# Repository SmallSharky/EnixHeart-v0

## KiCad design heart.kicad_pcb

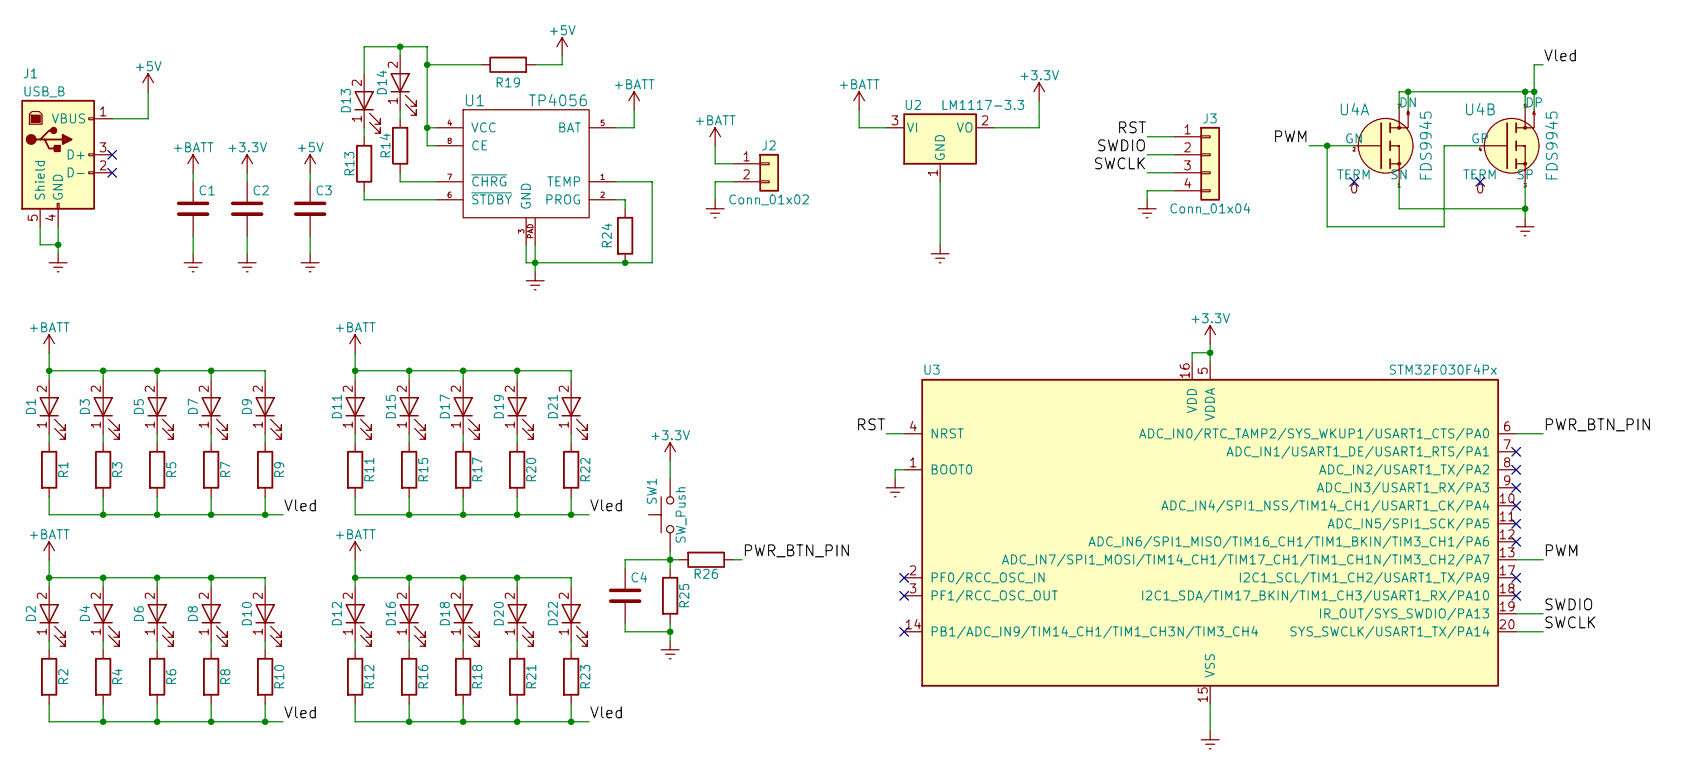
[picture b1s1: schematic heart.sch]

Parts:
C1, C2, C3, C4: C; C_0805_HandSoldering
D1, D2, D3, D4, D5, D6, D7, D8, D9, D10, D11, D12, D13, D14, D15, D16, D17, D18, D19, D20, D21, D22: LED; LED_1206_HandSoldering
J1: USB_B; USB_Micro-B_Molex_47346-0001
J2: Conn_01x02; Pin_Header_Straight_1x02_Pitch2.54mm
J3: Conn_01x04; Pin_Header_Straight_1x04_Pitch2.54mm
R1, R2, R3, R4, R5, R6, R7, R8, R9, R10, R11, R12, R13, R14, R15, R16, R17, R18, R19, R20, R21, R22, R23, R24, R25, R26: R; R_1206_HandSoldering
SW1: SW_Push; SW_SPST_EVQQ2
U1: TP4056; SOIC-8-1EP_3.9x4.9mm_Pitch1.27mm
U2: LM1117-3.3; SOT-223
U3: STM32F030F4Px; TSSOP-20_4.4x6.5mm_Pitch0.65mm
U4: FDS9945; SOIC-8_3.9x4.9mm_Pitch1.27mm

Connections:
+3V3: C2.1, SW1.2, U2.2 (VO), U3.5 (VDDA), U3.16 (VDD)
+5V: C3.1, J1.1 (VBUS), R19.2
+BATT: C1.1, D1.2 (A), D2.2 (A), D3.2 (A), D4.2 (A), D5.2 (A), D6.2 (A), D7.2 (A), D8.2 (A), D9.2 (A), D10.2 (A), D11.2 (A), D12.2 (A), D15.2 (A), D16.2 (A), D17.2 (A), D18.2 (A), D19.2 (A), D20.2 (A), D21.2 (A), D22.2 (A), J2.1, U1.5 (BAT), U2.3 (VI)
/PWM: U3.13 (ADC_IN7/SPI1_MOSI/TIM14_CH1/TIM17_CH1/T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), U4.2 (GN), U4.4 (GP)
/PWR_BTN_PIN: R26.1, U3.6 (ADC_IN0/RTC_TAMP2/SYS_WKUP1/USART1_CTS/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)
/RST: J3.1, U3.4 (NRST)
/SWCLK: J3.3, U3.20 (SYS_SWCLK/USART1_TX/PA14)
/SWDIO: J3.2, U3.19 (IR_OUT/SYS_SWDIO/PA13)
/Vled: R1.2, R2.2, R3.2, R4.2, R5.2, R6.2, R7.2, R8.2, R9.2, R10.2, R11.2, R12.2, R15.2, R16.2, R17.2, R18.2, R20.2, R21.2, R22.2, R23.2, U4.5, U4.6 (DP), U4.7, U4.8 (DN)
GNDREF: C1.2, C2.2, C3.2, C4.2, J1.4 (GND), J1.5 (Shield), J2.2, J3.4, R24.2, R25.2, U1.1 (TEMP), U1.3 (GND), U1.PAD, U2.1 (GND), U3.1 (BOOT0), U3.15 (VSS), U4.1 (SN), U4.3 (SP)
unnamed: C4.1, R25.1, R26.2, SW1.1
unnamed: D1.1 (K), R1.1
unnamed: D2.1 (K), R2.1
unnamed: D3.1 (K), R3.1
unnamed: D4.1 (K), R4.1
unnamed: D5.1 (K), R5.1
unnamed: D6.1 (K), R6.1
unnamed: D7.1 (K), R7.1
unnamed: D8.1 (K), R8.1
unnamed: D9.1 (K), R9.1
unnamed: D10.1 (K), R10.1
unnamed: D11.1 (K), R11.1
unnamed: D12.1 (K), R12.1
unnamed: D13.1 (K), R13.2
unnamed: D13.2 (A), D14.2 (A), R19.1, U1.4 (VCC), U1.8 (CE)
unnamed: D14.1 (K), R14.2
unnamed: D15.1 (K), R15.1
unnamed: D16.1 (K), R16.1
unnamed: D17.1 (K), R17.1
unnamed: D18.1 (K), R18.1
unnamed: D19.1 (K), R20.1
unnamed: D20.1 (K), R21.1
unnamed: D21.1 (K), R22.1
unnamed: D22.1 (K), R23.1
unnamed: R13.1, U1.6 (~STDBY)
unnamed: R14.1, U1.7 (~CHRG)
unnamed: R24.1, U1.2 (PROG)

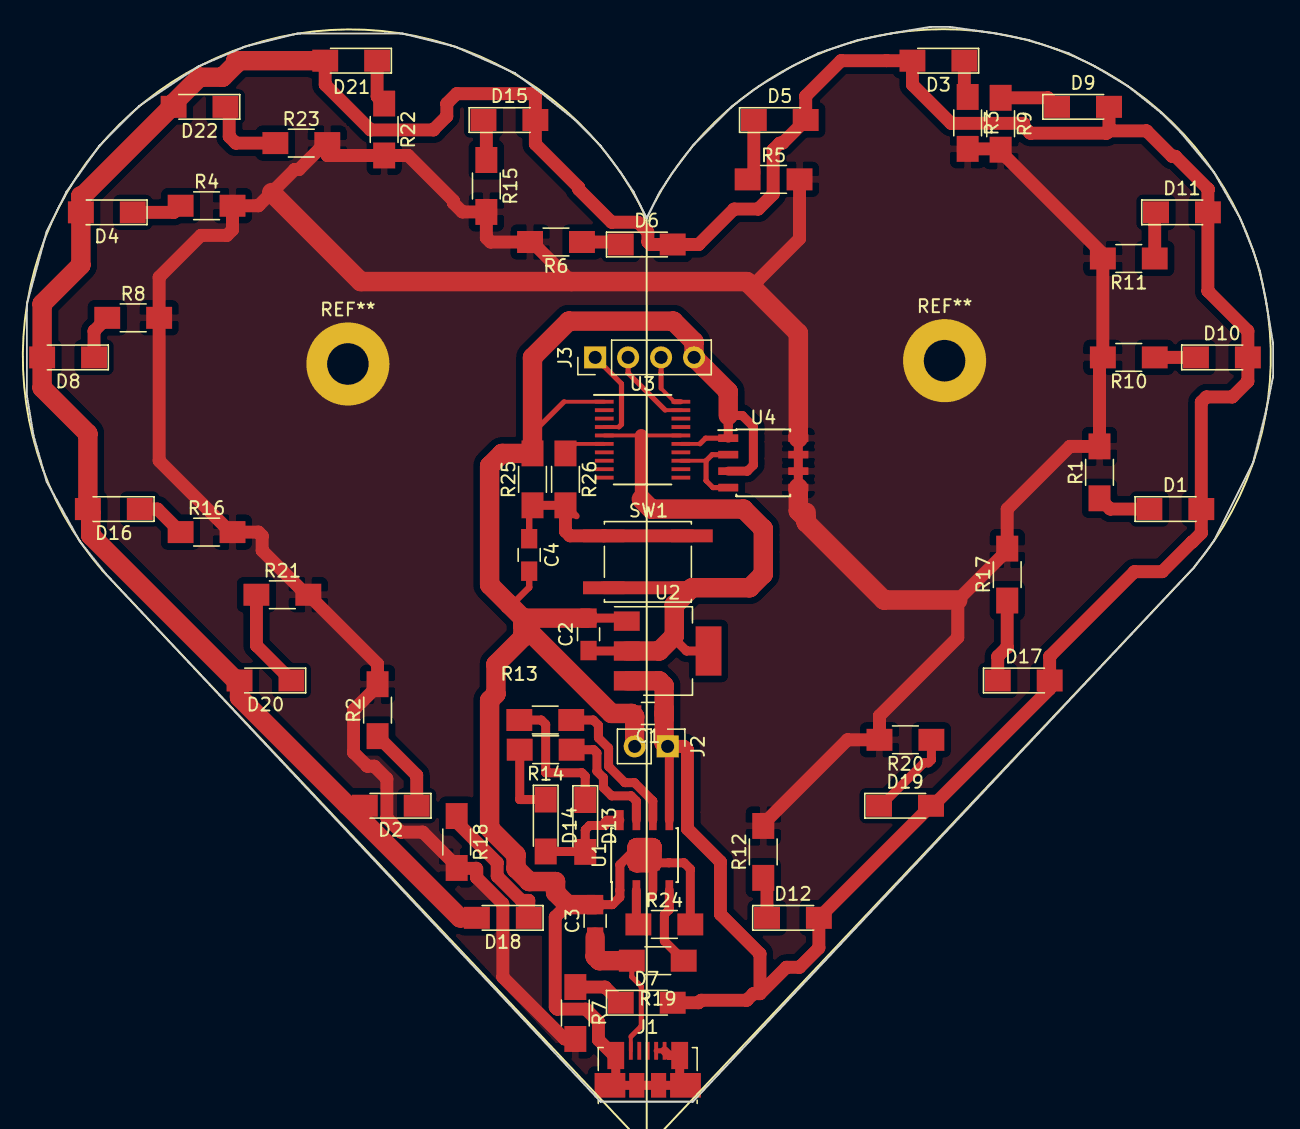
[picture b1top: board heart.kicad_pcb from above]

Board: 2 copper layers, 96.0 x 82.8 mm, 60 parts (0 on the bottom side), 37 nets.

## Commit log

2017-12-23 Init
2017-12-23 Down add
